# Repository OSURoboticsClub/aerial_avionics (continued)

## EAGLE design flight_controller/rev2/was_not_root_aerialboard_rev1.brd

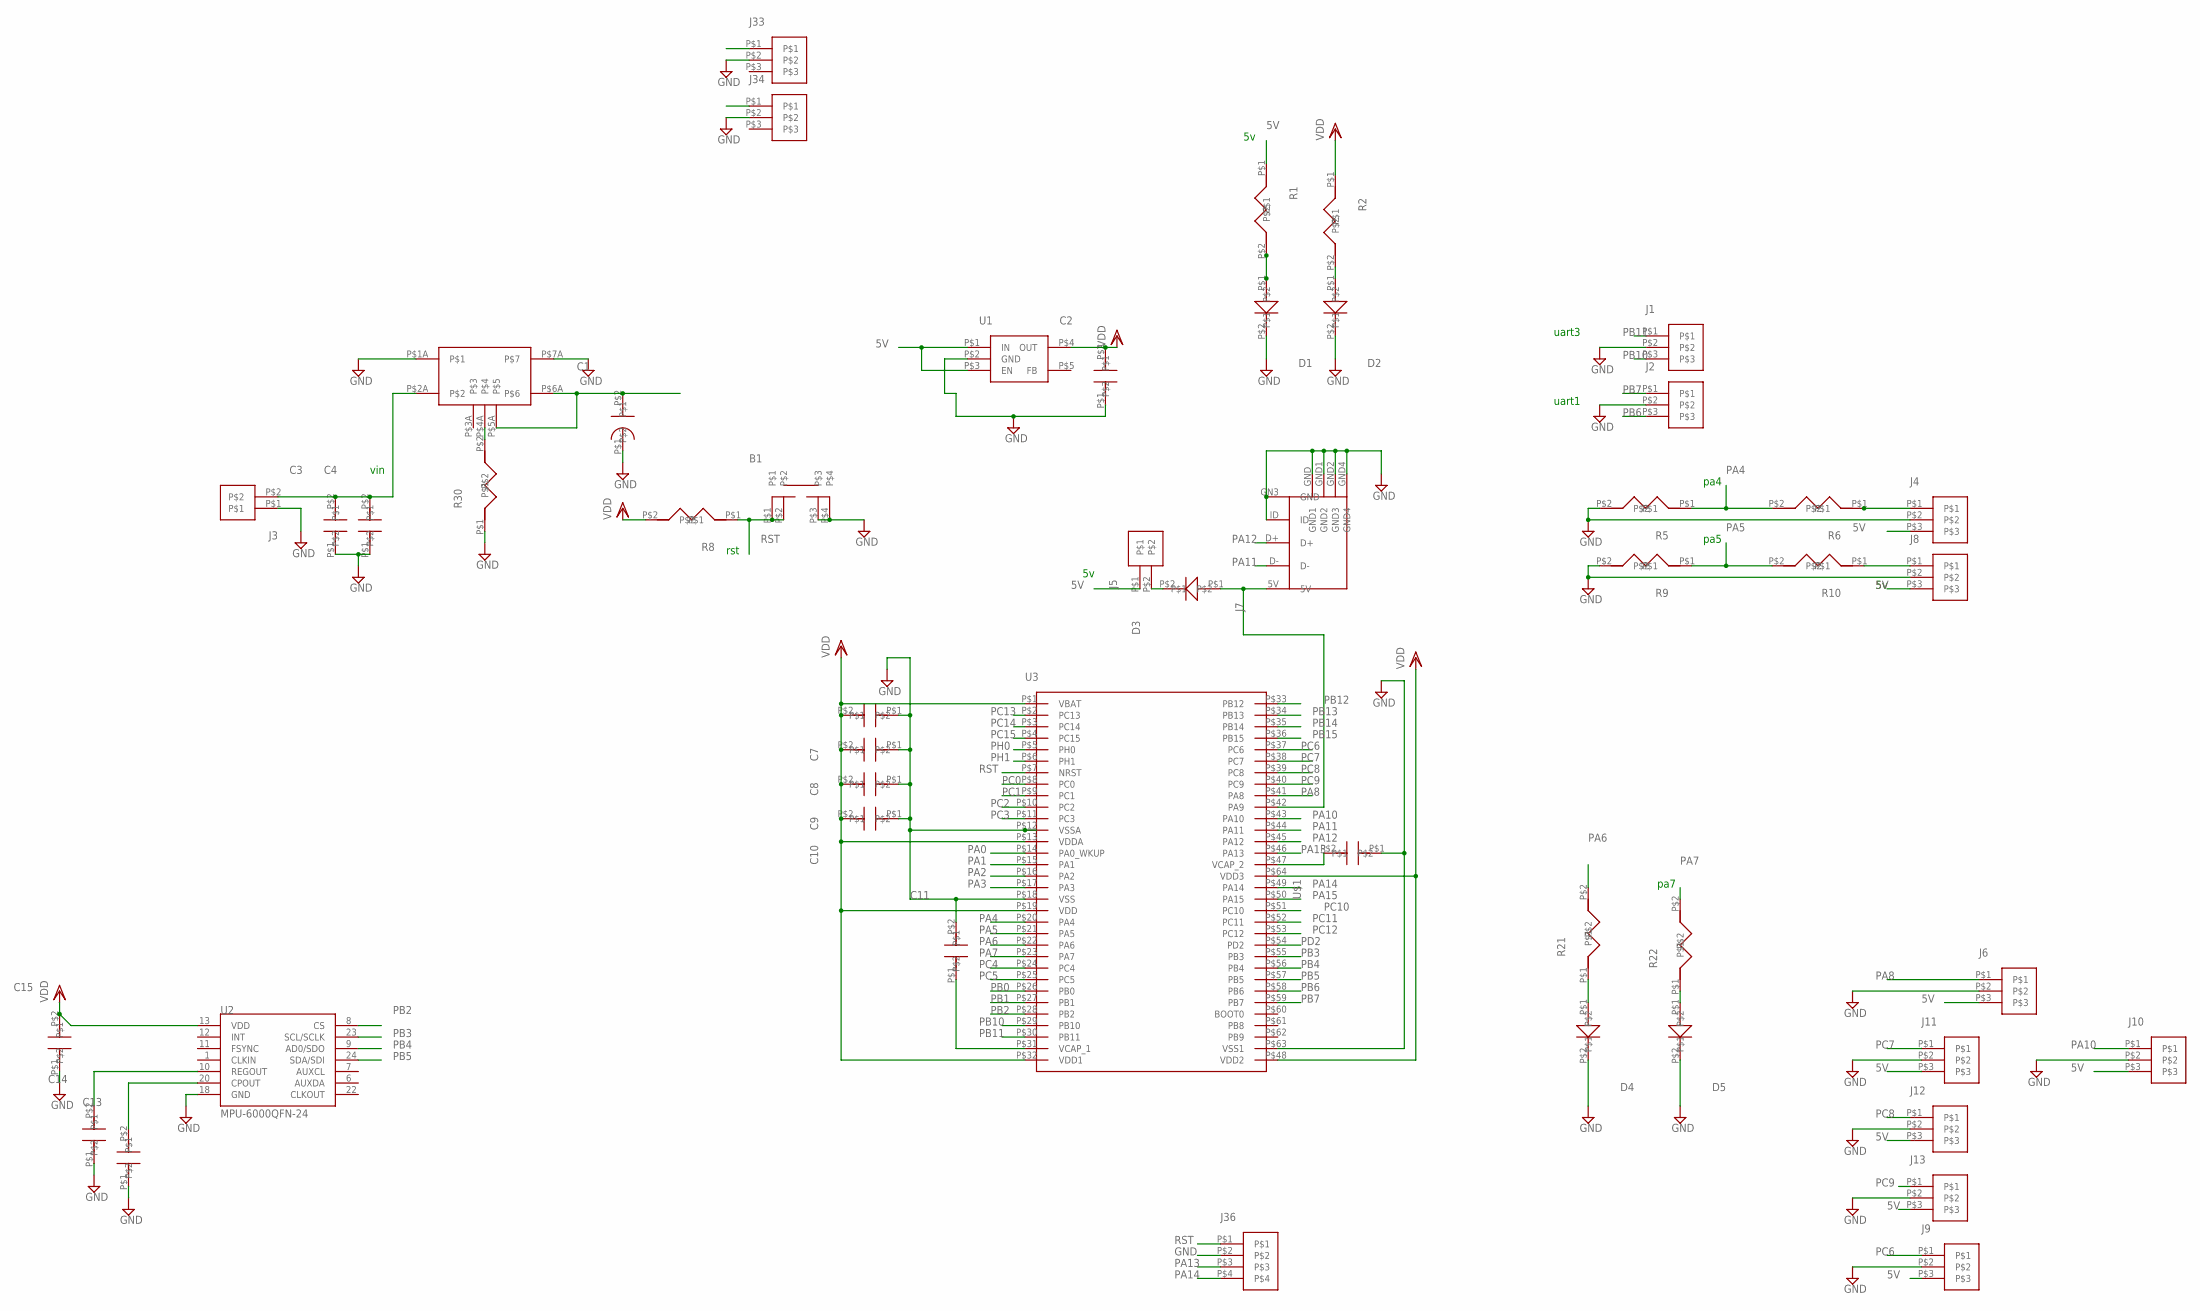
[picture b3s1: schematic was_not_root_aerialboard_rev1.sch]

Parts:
B1: SM-BUTTON; SM_BUTTON
C1: CAPACITOR-330UF; 330UF-CAPACITOR
C2, C3, C4, C11: 2.2UF-CAP; 0603-CAPACITOR
C7, C8, C9, C14, C15: CAPACITOR-.1UF-4V; 0603-CAPACITOR
C10: 4.7UF-CAP6.3V; 0603-CAPACITOR
C13: CAPACITOR-2.2NF-50V; 0603-CAPACITOR
D1, D2, D4: RED_LED; 0603-CAPACITOR
D3: B240A-DIODE; DIODE-DS13004
D5: ORANGE_LED; 0603-CAPACITOR
J1, J2, J4, J6, J8, J9, J10, J11, J12, J13: 3-PIN-SHERLOCK; 3-PIN-2MM
J3: 2-PIN-POWER; 2-PIN-3MM
J5: 2-PIN-100MIL; 2PIN-100MIL
J7: USB_MINI_B
J33, J34: 3-PIN-3MM
J36: 4-PIN-SHERLOCK; 4-PIN-2MM
R1, R2, R8, R21, R22: RESISTOR-4.7K-25V; 0603-CAPACITOR
R5, R6, R9, R10: 10K_RESISTOR; 0603-CAPACITOR
R30: 21K_RESISTOR; 0603-CAPACITOR
U1: TPS73433-3.3-REG; TPS73433-SOT5
U2: MPU-6000QFN-24; QFN-24-TESTING
U3: STM32F405RG; LQFP-64-STM32F405
U$1: 2.2UF-CAP; 0603-CAPACITOR
U$2: WIDE_IN_REG

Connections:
5V: C1.P$2, J4.P$3, J5.P$1, J6.P$3, J8.P$3, J9.P$3, J10.P$3, J11.P$3, J12.P$3, J13.P$3, J33.P$1, J34.P$1, R1.P$1, U1.P$1 (IN), U1.P$3 (EN), U$2.P$5A, U$2.P$6A
GND: B1.P$3, B1.P$4, C1.P$1, C2.P$1, C3.P$1, C4.P$1, C7.P$1, C8.P$1, C9.P$1, C10.P$1, C11.P$2, C13.P$1, C14.P$1, C15.P$1, D1.P$2, D2.P$2, D4.P$2, D5.P$2, J1.P$2, J2.P$2, J3.P$1, J4.P$2, J6.P$2, J7.GN3 (GND), J7.GND (GND1), J7.GND1 (GND2), J7.GND2 (GND3), J7.GND4, J7.ID, J8.P$2, J9.P$2, J10.P$2, J11.P$2, J12.P$2, J13.P$2, J33.P$2, J34.P$2, J36.P$2, R5.P$2, R9.P$2, R30.P$1, U1.P$2 (GND), U2.18 (GND), U3.P$12 (VSSA), U3.P$18 (VSS), U3.P$63 (VSS1), U$1.P$1, U$2.P$1A, U$2.P$7A
unnamed: C13.P$2, U2.20 (CPOUT)
unnamed: D3.P$2, J5.P$2
unnamed: J4.P$1, R6.P$1
unnamed: D4.P$1, R21.P$1
unnamed: R30.P$2, U$2.P$4A
unnamed: J8.P$1, R10.P$1
unnamed: D5.P$1, R22.P$1
unnamed: U3.P$47 (VCAP_2), U$1.P$2
unnamed: C11.P$1, U3.P$31 (VCAP_1)
unnamed: D2.P$1, R2.P$2
unnamed: D1.P$1, R1.P$2
unnamed: C14.P$2, U2.10 (REGOUT)
PA0: U3.P$14 (PA0_WKUP)
PA1: U3.P$15 (PA1)
PA2: U3.P$16 (PA2)
PA3: U3.P$17 (PA3)
PA4: R5.P$1, R6.P$2, U3.P$20 (PA4)
PA5: R9.P$1, R10.P$2, U3.P$21 (PA5)
PA6: R21.P$2, U3.P$22 (PA6)
PA7: R22.P$2, U3.P$23 (PA7)
PA8: J6.P$1, U3.P$41 (PA8)
PA9: D3.P$1, J7.5V, U3.P$42 (PA9)
PA10: J10.P$1, U3.P$43 (PA10)
PA11: J7.D-, U3.P$44 (PA11)
PA12: J7.D+, U3.P$45 (PA12)
PA13: J36.P$3, U3.P$46 (PA13)
PA14: J36.P$4, U3.P$49 (PA14)
PA15: U3.P$50 (PA15)
PB0: U3.P$26 (PB0)
PB1: U3.P$27 (PB1)
PB2: U2.8 (CS), U3.P$28 (PB2)
PB3: U2.23 (SCL/SCLK), U3.P$55 (PB3)
PB4: U2.9 (AD0/SDO), U3.P$56 (PB4)
PB5: U2.24 (SDA/SDI), U3.P$57 (PB5)
PB6: J2.P$3, U3.P$58 (PB6)
PB7: J2.P$1, U3.P$59 (PB7)
PB10: J1.P$3, U3.P$29 (PB10)
PB11: J1.P$1, U3.P$30 (PB11)
PB12: U3.P$33 (PB12)
PB13: U3.P$34 (PB13)
PB14: U3.P$35 (PB14)
PB15: U3.P$36 (PB15)
PC0: U3.P$8 (PC0)
PC1: U3.P$9 (PC1)
PC2: U3.P$10 (PC2)
PC3: U3.P$11 (PC3)
PC4: U3.P$24 (PC4)
PC5: U3.P$25 (PC5)
PC6: J9.P$1, U3.P$37 (PC6)
PC7: J11.P$1, U3.P$38 (PC7)
PC8: J12.P$1, U3.P$39 (PC8)
PC9: J13.P$1, U3.P$40 (PC9)
PC10: U3.P$51 (PC10)
PC11: U3.P$52 (PC11)
PC12: U3.P$53 (PC12)
PC13: U3.P$2 (PC13)
PC14: U3.P$3 (PC14)
PC15: U3.P$4 (PC15)
PD2: U3.P$54 (PD2)
PH0: U3.P$5 (PH0)
PH1: U3.P$6 (PH1)
RST: B1.P$1, B1.P$2, J36.P$1, R8.P$1, U3.P$7 (NRST)
VDD: C2.P$2, C7.P$2, C8.P$2, C9.P$2, C10.P$2, C15.P$2, R2.P$1, R8.P$2, U1.P$4 (OUT), U2.13 (VDD), U3.P$1 (VBAT), U3.P$13 (VDDA), U3.P$19 (VDD), U3.P$32 (VDD1), U3.P$48 (VDD2), U3.P$64 (VDD3)
VIN: C3.P$2, C4.P$2, J3.P$2, U$2.P$2A

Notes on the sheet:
vin
pa4
pa5
pa7
rst
uart3
uart1

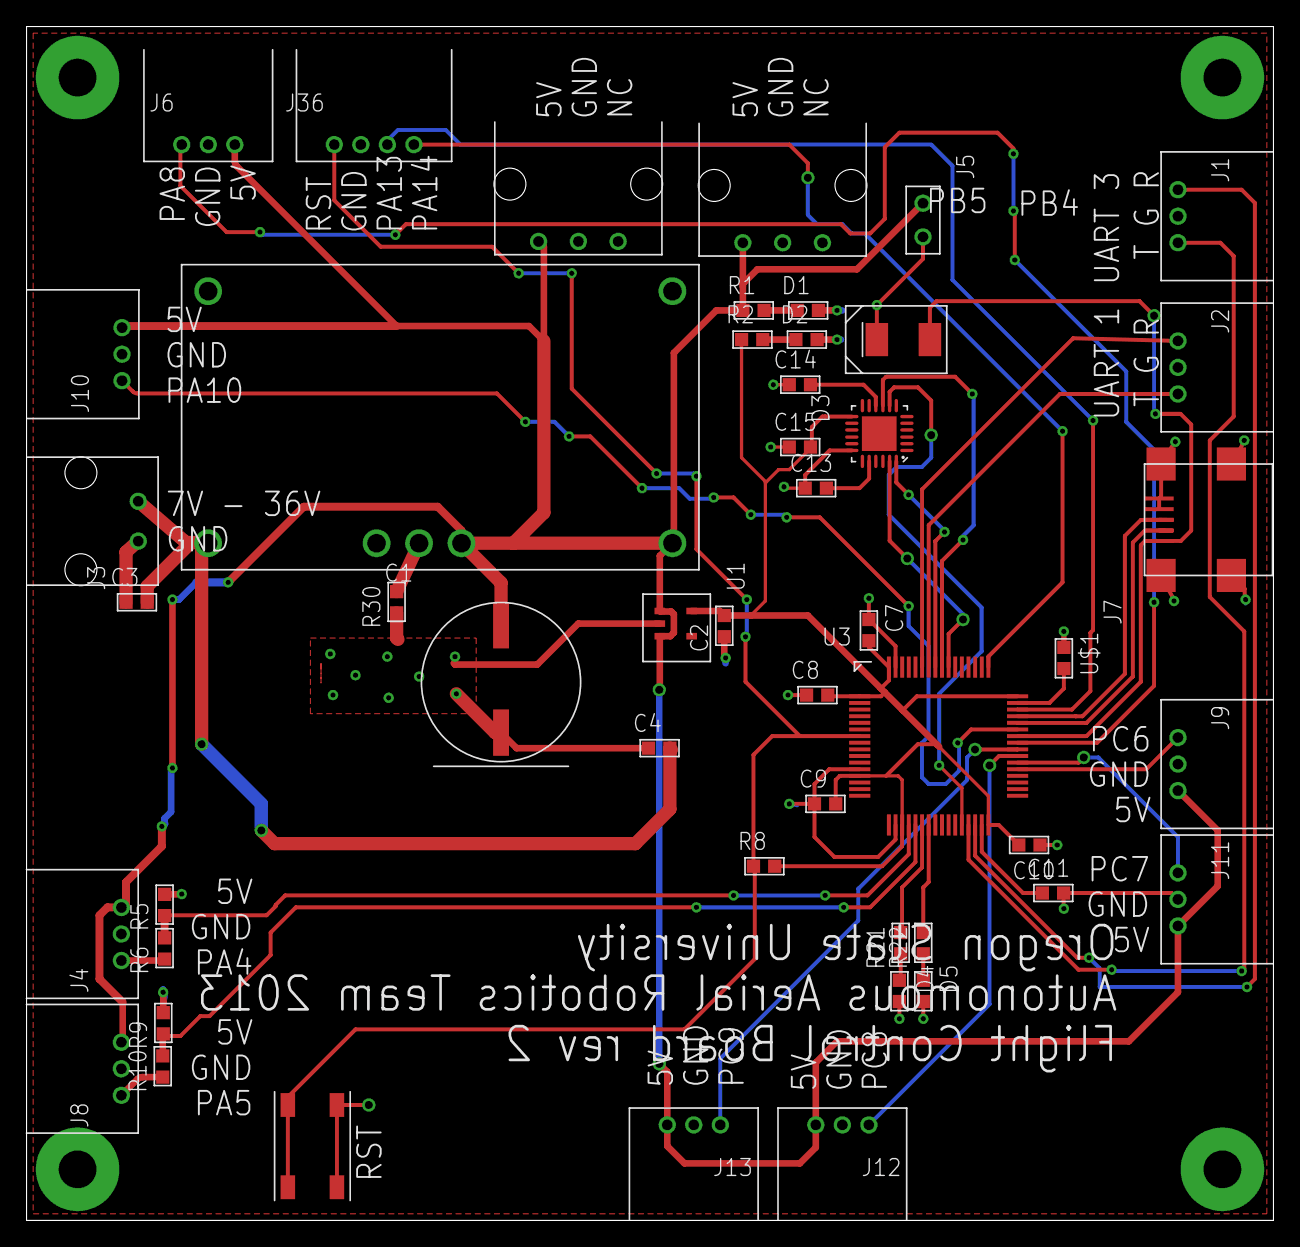
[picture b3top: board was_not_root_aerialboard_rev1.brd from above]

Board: 2 copper layers, 94.0 x 90.0 mm, 49 parts (0 on the bottom side), 40 nets.

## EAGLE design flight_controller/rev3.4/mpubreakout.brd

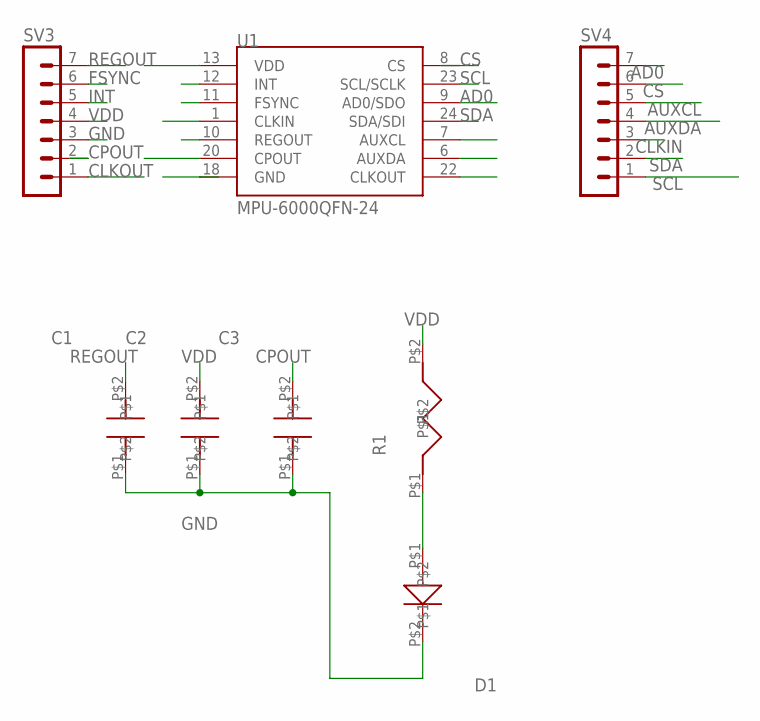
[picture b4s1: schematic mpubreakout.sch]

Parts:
C1, C2: CAPACITOR-.1UF-4V; 0603-CAPACITOR
C3: CAPACITOR-2.2NF-50V; 0603-CAPACITOR
D1: RED_LED; 0603-CAPACITOR
R1: RESISTOR-4.7K-25V; 0603-CAPACITOR
SV3, SV4: MA07-1
U1: MPU-6000QFN-24; QFN-24-TESTING

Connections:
AD0: SV4.7, U1.9 (AD0/SDO)
AUXCL: SV4.5, U1.7 (AUXCL)
AUXDA: SV4.4, U1.6 (AUXDA)
CLKIN: SV4.3, U1.1 (CLKIN)
CLKOUT: SV3.1, U1.22 (CLKOUT)
CPOUT: C3.P$2, SV3.2, U1.20 (CPOUT)
CS: SV4.6, U1.8 (CS)
FSYNC: SV3.6, U1.11 (FSYNC)
GND: C1.P$1, C2.P$1, C3.P$1, D1.P$2, SV3.3, U1.18 (GND)
INT: SV3.5, U1.12 (INT)
unnamed: D1.P$1, R1.P$1
REGOUT: C1.P$2, SV3.7, U1.10 (REGOUT)
SCL: SV4.1, U1.23 (SCL/SCLK)
SDA: SV4.2, U1.24 (SDA/SDI)
VDD: C2.P$2, R1.P$2, SV3.4, U1.13 (VDD)

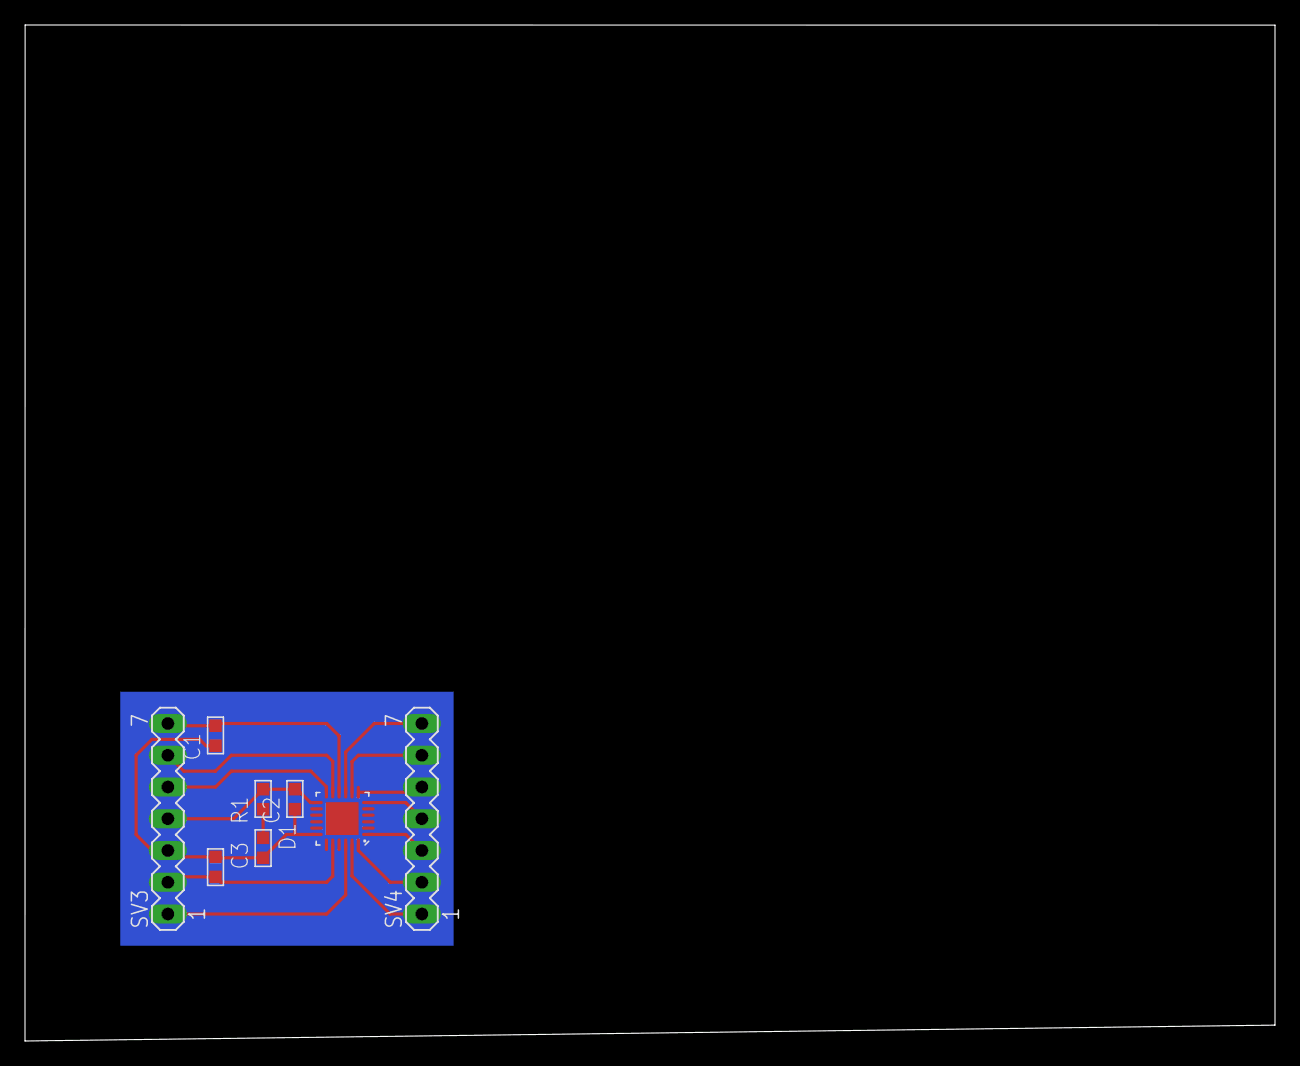
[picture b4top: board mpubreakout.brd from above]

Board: 2 copper layers, 100.0 x 81.3 mm, 8 parts (0 on the bottom side), 15 nets.

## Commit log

2014-11-05 Add readme.
2014-11-05 Add sparkfun eagle libs as submodule.
2014-11-05 Add FC board revs 0, 1, 2, and 3.4.
2014-11-05 Add ESC rev1.
2014-11-05 Add ESC rev2.
2014-12-15 Copy rev3.4 to core.{brd,sch}.
    This will be our version-controlled copy of the board.
2014-12-16 Remove Sparkfun eagle libraries as submodule.
2014-12-16 Start reorganizing. F4 logic power copied.
    Need to verify this was correct to begin with.
2014-12-17 Redraw schematics for PWM, ADC, SWD.
2014-12-17 Split F4 into GPIO and POWER subcomponents.
2014-12-18 Add gitignore.
2014-12-18 Move things around.
2014-12-18 Replace Incorrect Parts
2014-12-18 Add LEDs for F4, XBee, power.
2014-12-18 Added Capacitor to 3.3V Regulator
2014-12-18 Clean up 3.3V reg.
2014-12-18 ADD DEBUG LEDS
    EDA does not lend itself to easy version control.
2014-12-18 Add Kill BJTs, reset button, uSD and USB connectors.
2014-12-18 Add more LEDs.
2014-12-18 Update connectors and start drawing SPI/I2C breakout.
    Hella progress yo.
2014-12-18 Add MPU-6000, more bypass caps, replace various packages for consistency.
2014-12-19 Add some missing junctions.
2014-12-19 Add roadmap.
2014-12-19 Rephrase.
2014-12-19 Add MS5611 circuit and SPI and I2C pullup/down resistors.
2014-12-19 Rename some nets.
2014-12-19 Add oscillator.
2014-12-21 Replace XBee headers with SMD variant.
2014-12-21 Reassign and rename UART buses to XBee and GPS.
2014-12-21 Explicitly name XBee package.
2014-12-21 Remove XBee reset pin from global reset net.
    The XBee pin is for factory resetting the device! Read the datasheet, people!
2014-12-21 Add blurb about how this is a dev version.
2014-12-21 Add RGB status LED pair.
2014-12-22 Replace components to those from new OSURC libraries.
2014-12-22 Change kill BJTs to dual N-ch MOSFETs.
2014-12-22 Replace LED MOSFETs with dual-channel MOSFETs.
2014-12-26 Remove 5V regulator todo and add reverse voltage protection.
    Board will need 5V input from external regulator.
2014-12-27 Add TVS/RVP circuit.
2014-12-27 Implement MPU-9250.
2014-12-27 Move some things around.
2014-12-27 Update v4.0 changelog.
2014-12-29 Add digital I/O pins, remove some LEDs, rearrange stuff.
2014-12-29 Resolve most ERC errors.
    Two warnings for unused F4's B12 and C15.
2014-12-29 Renumber schematic.
2014-12-31 Add test points.
2014-12-31 Update connectors with those from OSURC libs.
    Dunno how these didn't get updated last time.
2014-12-31 Correct symbol placement.
2014-12-31 Start layout.
2014-12-31 Connect KILL with a stray KILL1 net.
2014-12-31 Remove value from MPU footprint.
2015-01-01 Move USB 5V to VIN.
2015-01-01 Make last two PWM outputs 5V powered (for servos).
2015-01-01 Component placement almost done, routing halfway done.
2015-01-01 More layout, and replace passives with OSURC's own.
2015-01-01 Layout 70% done with new 8MHz crystal.
2015-01-02 FC layout 90% done.
2015-01-02 Resolve all errors and finish routing.
2015-01-05 Space out some unnecessarily closely-spaced traces.
2015-01-12 Add USB diffpair net class and USB termination resistors.
2015-01-12 Place USB termination resistors.
2015-01-12 Finish up.
2015-01-12 Place new uSD socket and LEDs.
2015-01-12 Place testpoint labels properly.
2015-01-12 Add gyro axis indicator on silkscreen.
2015-01-12 Add note on board thickness.
2015-01-13 Add missing trace.
    Dunno how that went missing.
2015-01-13 Swap out MIC5219 3.3V linreg with our own symbol.
2015-01-13 Use own XBee symbol.
2015-01-14 Place new USB connector.
2015-01-14 Remove some resolved todos.
2015-01-14 Update USB connector.
2015-01-14 Add more silkscreen guides.
2015-01-14 Add DFRobot CAM.
2015-01-15 Tweak silkscreen.
2015-01-16 Add v3.9 fab files.
2015-01-16 Update v3.9 changelog.
2015-01-16 Update layout PDF.
2015-01-24 Start FCv4.0 in Altium.
2015-01-24 Add cover properly.
2015-01-24 Copy F4 pin config.
2015-02-05 Add dru.
2015-03-20 Add Drake's power distribution board schematics and beginnings of layout.
2015-03-20 Add extra Vin connector to pdb schematic
2016-01-24 Remove old altium version of v4.0
2016-01-24 Fix MPU-9250 footprint.
2016-01-24 Add FC v3.9.1.
    This fixes the bad MPU-9250 footprint.
